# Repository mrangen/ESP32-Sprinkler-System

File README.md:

# ESP32 Sprinkler System
 An ESP32 based wireless sprinkler control system for use with Home Assistant.

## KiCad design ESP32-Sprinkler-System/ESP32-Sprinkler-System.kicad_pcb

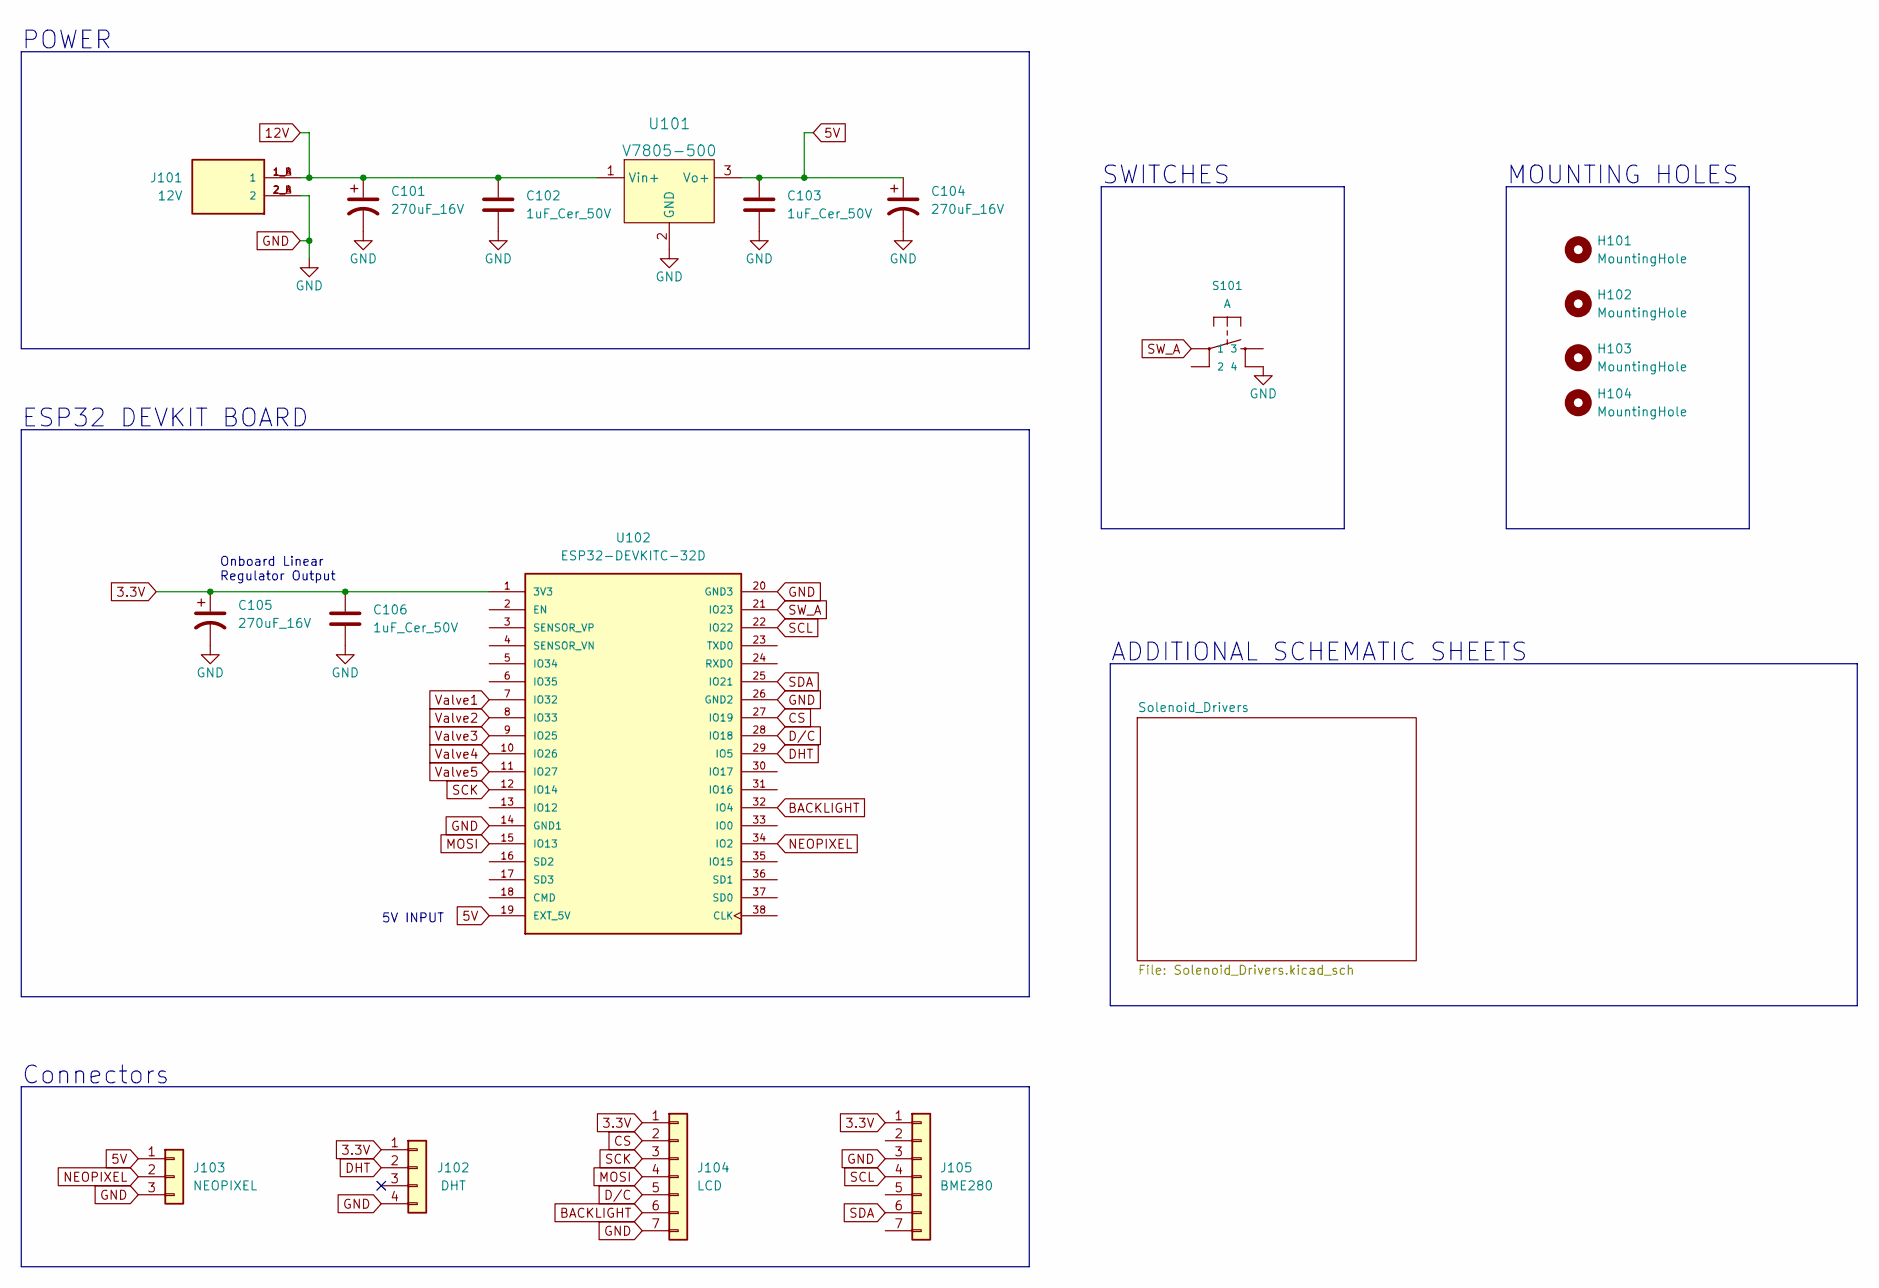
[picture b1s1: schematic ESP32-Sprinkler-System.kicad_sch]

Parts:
C101, C104, C105: 270uF_16V; CP_Radial_D6.3mm_P2.50mm
C102, C103, C106: 1uF_Cer_50V; C_Disc_D7.5mm_W4.4mm_P5.00mm
H101, H102, H103, H104: MountingHole; MountingHole_3.2mm_M3
J101: 12V; CUI_TBL004-508-02BE-2GY
J102: DHT; PinSocket_1x04_P2.54mm_Vertical
J103: NEOPIXEL; PinSocket_1x03_P2.54mm_Vertical
J104: LCD; PinSocket_1x07_P2.54mm_Vertical
J105: BME280; PinSocket_1x07_P2.54mm_Vertical
S101: A; TACTILE_SWITCH_PTH_12MM
U101: V7805-500; 3-SIP_Module_V7805-500; MPN V7805-500; Digi-Key_PN 102-1709-ND
U102: ESP32-DEVKITC-32D; MODULE_ESP32-DEVKITC-32D; PARTREV 4

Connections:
3.3V: C105.1, C106.1, J102.1, J104.1, J105.1, U102.1 (3V3)
5V: C103.1, C104.1, J103.1, U101.3 (Vo+), U102.19 (EXT_5V)
12V: C101.1, C102.1, J101.1_A (1), J101.1_B (1), U101.1 (Vin+); also elsewhere on the board
BACKLIGHT: J104.6, U102.32 (IO4)
CS: J104.2, U102.27 (IO19)
DHT: J102.2, U102.29 (IO5)
D/C: J104.5, U102.28 (IO18)
GND: C101.2, C102.2, C103.2, C104.2, C105.2, C106.2, J101.2_A (2), J101.2_B (2), J102.4, J103.3, J104.7, J105.3, S101.4, U101.2 (GND), U102.14 (GND1), U102.20 (GND3), U102.26 (GND2); also elsewhere on the board
MOSI: J104.4, U102.15 (IO13)
NEOPIXEL: J103.2, U102.34 (IO2)
SCK: J104.3, U102.12 (IO14)
SCL: J105.4, U102.22 (IO22)
SDA: J105.6, U102.25 (IO21)
SW_A: S101.1, U102.21 (IO23)
Valve1: U102.7 (IO32); also elsewhere on the board
Valve2: U102.8 (IO33); also elsewhere on the board
Valve3: U102.9 (IO25); also elsewhere on the board
Valve4: U102.10 (IO26); also elsewhere on the board
Valve5: U102.11 (IO27)

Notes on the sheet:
SWITCHES
MOUNTING HOLES
ESP32 DEVKIT BOARD
ADDITIONAL SCHEMATIC SHEETS
Onboard Linear Regulator Output
Connectors
POWER
5V INPUT

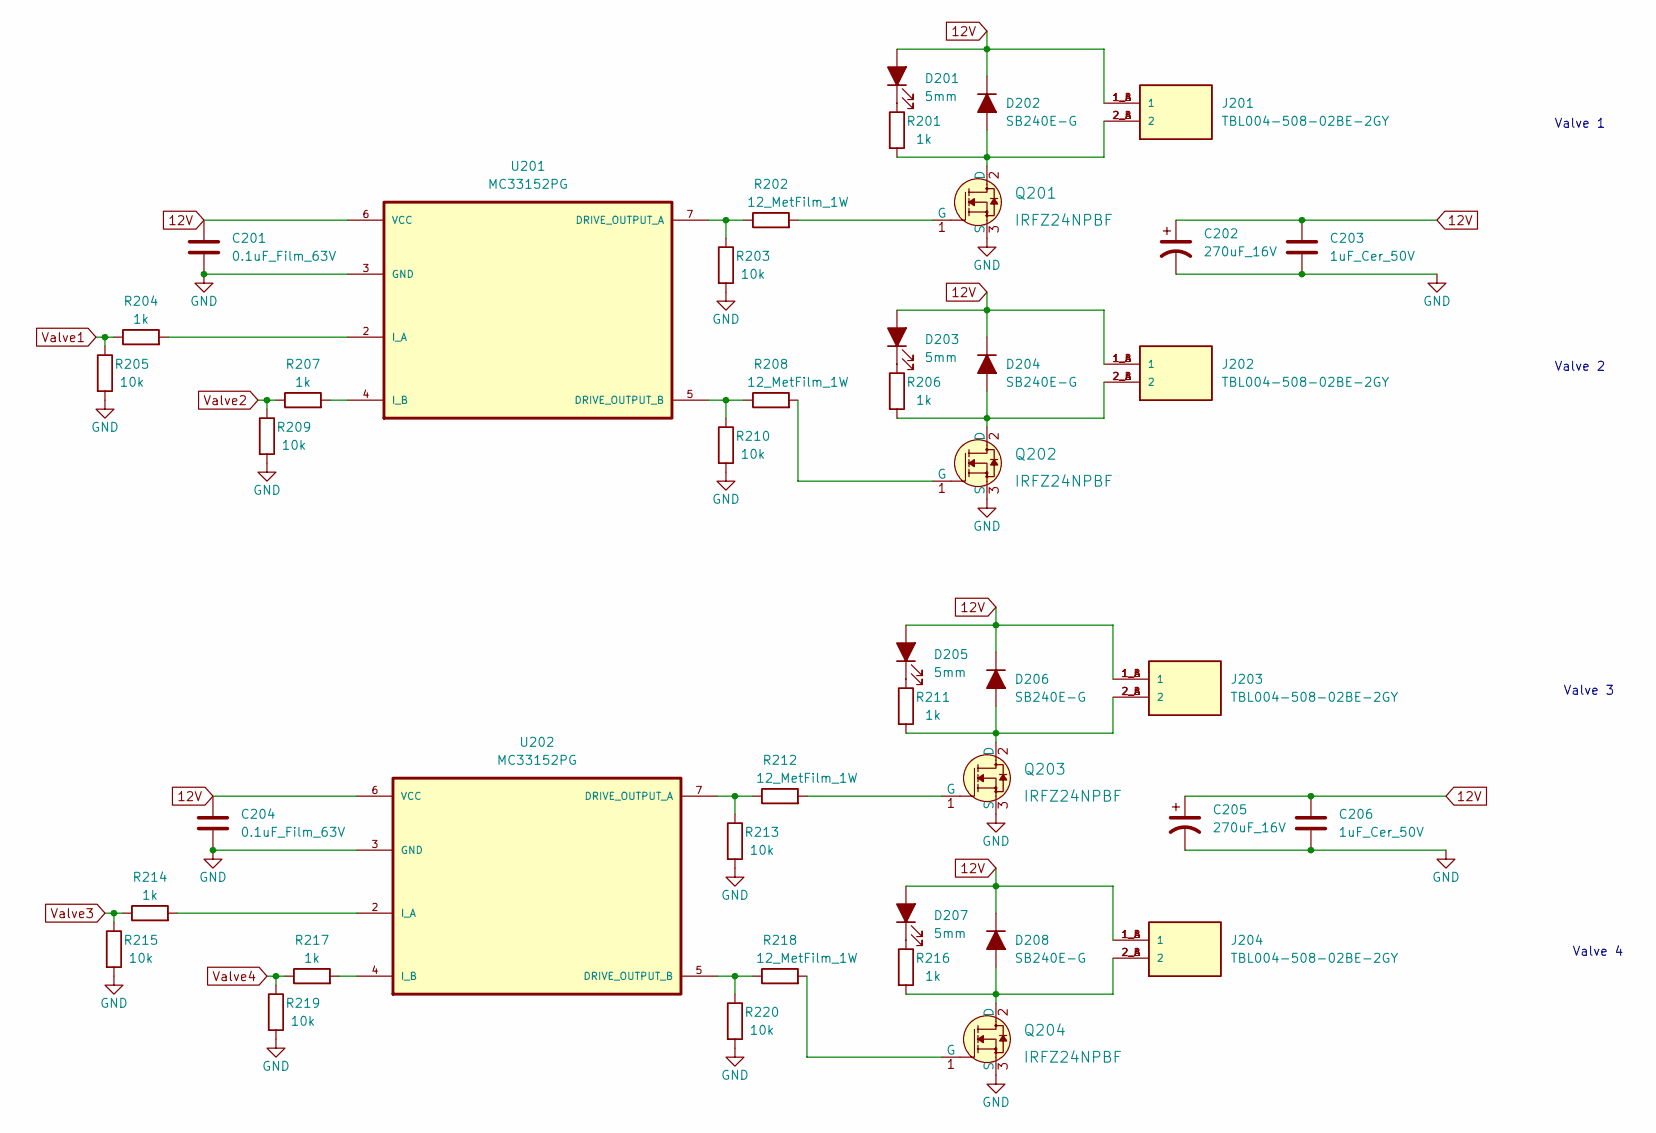
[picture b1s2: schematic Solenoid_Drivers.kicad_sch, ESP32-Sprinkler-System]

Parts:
C201, C204: 0.1uF_Film_63V; C_Rect_L7.0mm_W2.5mm_P5.00mm
C202, C205: 270uF_16V; CP_Radial_D6.3mm_P2.50mm
C203, C206: 1uF_Cer_50V; C_Disc_D7.5mm_W4.4mm_P5.00mm
D201, D203, D205, D207: 5mm; LED_D5.0mm
D202, D204, D206, D208: SB240E-G; D_DO-15_P12.70mm_Horizontal
J201, J202, J203, J204: TBL004-508-02BE-2GY; CUI_TBL004-508-02BE-2GY
Q201, Q202, Q203, Q204: IRFZ24NPBF; TO-220-3_Vertical; MPN IRF510PBF; Digi-Key_PN IRF510PBF-ND
R201, R204, R206, R207, R211, R214, R216, R217: 1k; R_Axial_DIN0207_L6.3mm_D2.5mm_P10.16mm_Horizontal
R202, R208, R212, R218: 12_MetFilm_1W; R_Axial_DIN0207_L6.3mm_D2.5mm_P10.16mm_Horizontal
R203, R205, R209, R210, R213, R215, R219, R220: 10k; R_Axial_DIN0207_L6.3mm_D2.5mm_P10.16mm_Horizontal
U201, U202: MC33152PG; DIP-8_W7.62mm; MPN MC33152PG

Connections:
12V: C201.1, C202.1, C203.1, C204.1, C205.1, C206.1, D201.2 (A), D202.1 (K), D203.2 (A), D204.1 (K), D205.2 (A), D206.1 (K), D207.2 (A), D208.1 (K), J201.1_A (1), J201.1_B (1), J202.1_A (1), J202.1_B (1), J203.1_A (1), J203.1_B (1), J204.1_A (1), J204.1_B (1), U201.6 (VCC), U202.6 (VCC); also elsewhere on the board
GND: C201.2, C202.2, C203.2, C204.2, C205.2, C206.2, Q201.3 (S), Q202.3 (S), Q203.3 (S), Q204.3 (S), R203.2, R205.2, R209.2, R210.2, R213.2, R215.2, R219.2, R220.2, U201.3 (GND), U202.3 (GND); also elsewhere on the board
unnamed: D201.1 (K), R201.1
unnamed: D202.2 (A), J201.2_A (2), J201.2_B (2), Q201.2 (D), R201.2
unnamed: D203.1 (K), R206.1
unnamed: D204.2 (A), J202.2_A (2), J202.2_B (2), Q202.2 (D), R206.2
unnamed: D205.1 (K), R211.1
unnamed: D206.2 (A), J203.2_A (2), J203.2_B (2), Q203.2 (D), R211.2
unnamed: D207.1 (K), R216.1
unnamed: D208.2 (A), J204.2_A (2), J204.2_B (2), Q204.2 (D), R216.2
unnamed: Q201.1 (G), R202.2
unnamed: Q202.1 (G), R208.2
unnamed: Q203.1 (G), R212.2
unnamed: Q204.1 (G), R218.2
unnamed: R202.1, R203.1, U201.7 (DRIVE_OUTPUT_A)
unnamed: R204.2, U201.2 (I_A)
unnamed: R207.2, U201.4 (I_B)
unnamed: R208.1, R210.1, U201.5 (DRIVE_OUTPUT_B)
unnamed: R212.1, R213.1, U202.7 (DRIVE_OUTPUT_A)
unnamed: R214.2, U202.2 (I_A)
unnamed: R217.2, U202.4 (I_B)
unnamed: R218.1, R220.1, U202.5 (DRIVE_OUTPUT_B)
Valve1: R204.1, R205.1; also elsewhere on the board
Valve2: R207.1, R209.1; also elsewhere on the board
Valve3: R214.1, R215.1; also elsewhere on the board
Valve4: R217.1, R219.1; also elsewhere on the board

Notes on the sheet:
Valve 2
Valve 4
Valve 1
Valve 3

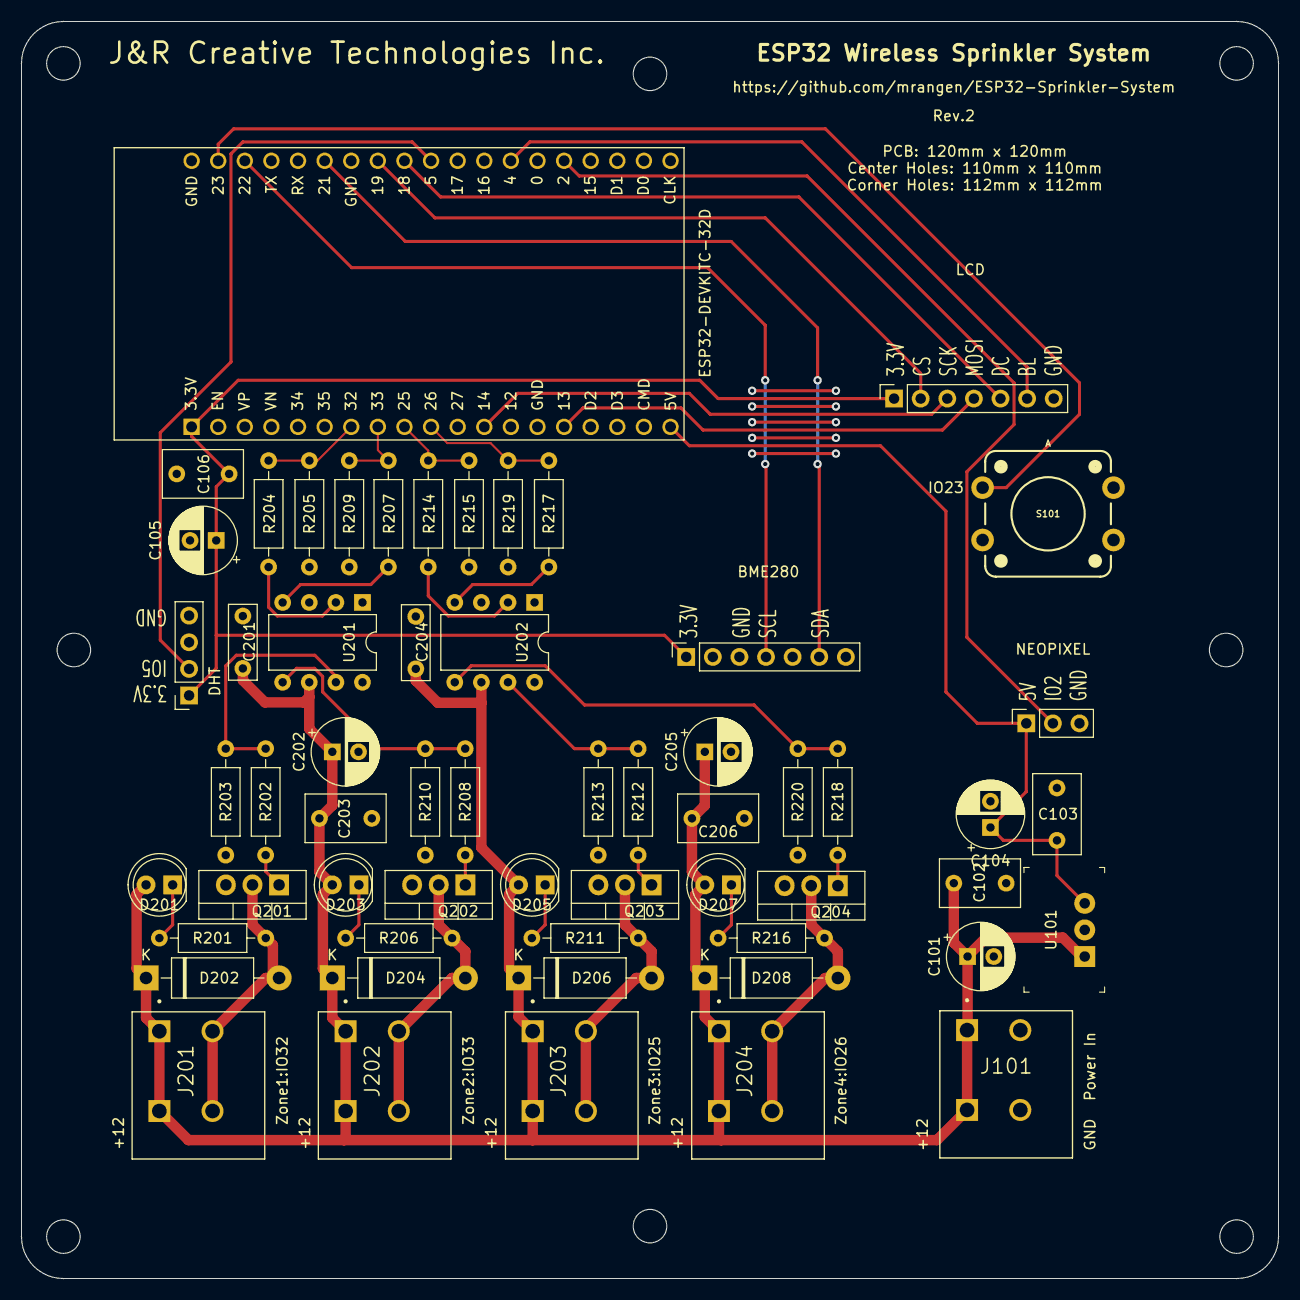
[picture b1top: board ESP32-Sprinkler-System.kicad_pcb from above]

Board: 2 copper layers, 120.0 x 120.0 mm, 66 parts (0 on the bottom side), 38 nets.

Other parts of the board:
H104#2, H104#3, H104#4, H104#5: MountingHole; MountingHole_3.2mm_M3

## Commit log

2022-05-29 Created KiCad Project
2022-05-29 Added Brainstorming Folder + Contents
2022-05-29 Created PCB File and got ESP32 files (sym,foot,step)
2022-05-29 3D models for most of the components.
2022-05-29 Need caps that can handle 12V
2022-06-07 Continued work on schematic
    Completed solenoid drivers.
    Working on Buck Converter.
2022-06-08 Continued working on schematic
    finished solenoid drivers, finished buck converter, started ESP32
2022-06-12 Added documentation for ESP32-DEVKITC-32E
    Going to use a devkit rather than a module, to speed up the project.
2022-06-22 Change of plans
    We had a change of plans. Rather than having everything made of surface-mount parts, we opted for a simpler through-hole project that could be breadboarded first. This circuit will be revisited and u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
2022-07-01 Major Update to New Through-Hole Components
    Circuit has been modified to match the breadboard prototype Cody built.
    Solenoid driver side is done.
2022-07-01 Found symbol and footprint for ESP32 DevKit, schematic 80% done.
2022-07-01 Schematic done, footprints assigned, terminal block requires footprint clarity, some 3D models missing.
2022-07-01 Remaining 3D models found/made
2022-07-08 Objs sorted like the schematic
2022-07-08 compact formation
2022-07-08 good layout.
2022-07-08 going to edit tracks
2022-07-08 done for today
2022-07-20 Traces complete
2022-07-20 Curvy lines
2022-07-20 curvy 2 saved
2022-07-21 added some labels and stuff
2022-07-27 TIDY UP AND ANOTATE
2022-07-29 Added M3 Mounting Holes
2022-07-29 Tidy up
    moved labels and reconnected traces
2022-07-30 Updated PCB
2022-07-30 Generated Gerbers
2022-08-09 Case model created
    main case built with cut out bodies made in freecad
2022-08-09 fixes to labels
2022-08-09 almost all parts made for case
2022-08-09 pcb standoffs
2022-08-09 added fonts
2022-08-09 fusions and spilt on plane
2022-08-09 moving files
2022-08-10 move file
2022-08-10 stl case v2 done
2022-08-10 saved
2022-08-10 gcode made
2022-08-10 case v3
2022-08-10 gcode
2022-08-12 added button system and LCD inset
2022-08-12 just before split
2022-08-12 case v4 stls made
2022-08-12 case split
2022-08-15 case top v5
2022-08-24 making new pcb 120x120mm
2022-08-24 new layout most in pos some traces ran
2022-08-25 4 new mount holes
2022-08-27 proper fit in box now
2022-08-28 Added comments to PCB in UserComments layer.
2022-08-28 finished fixes and trace placement.
    mike needs to review
2022-08-30 started creating a mount
2022-08-30 rev1 done
    print me
2022-08-30 mount Rev2
2022-08-30 rev1 stl
2022-08-31 adjusted top holes down a tiny
2022-08-31 made a solenoid cover
2022-09-01 adjusting
2022-09-02 solenoid cover rev2

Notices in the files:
ESP32-Sprinkler-System/ESP32-Sprinkler-System.kicad_pcb:
MIT License
